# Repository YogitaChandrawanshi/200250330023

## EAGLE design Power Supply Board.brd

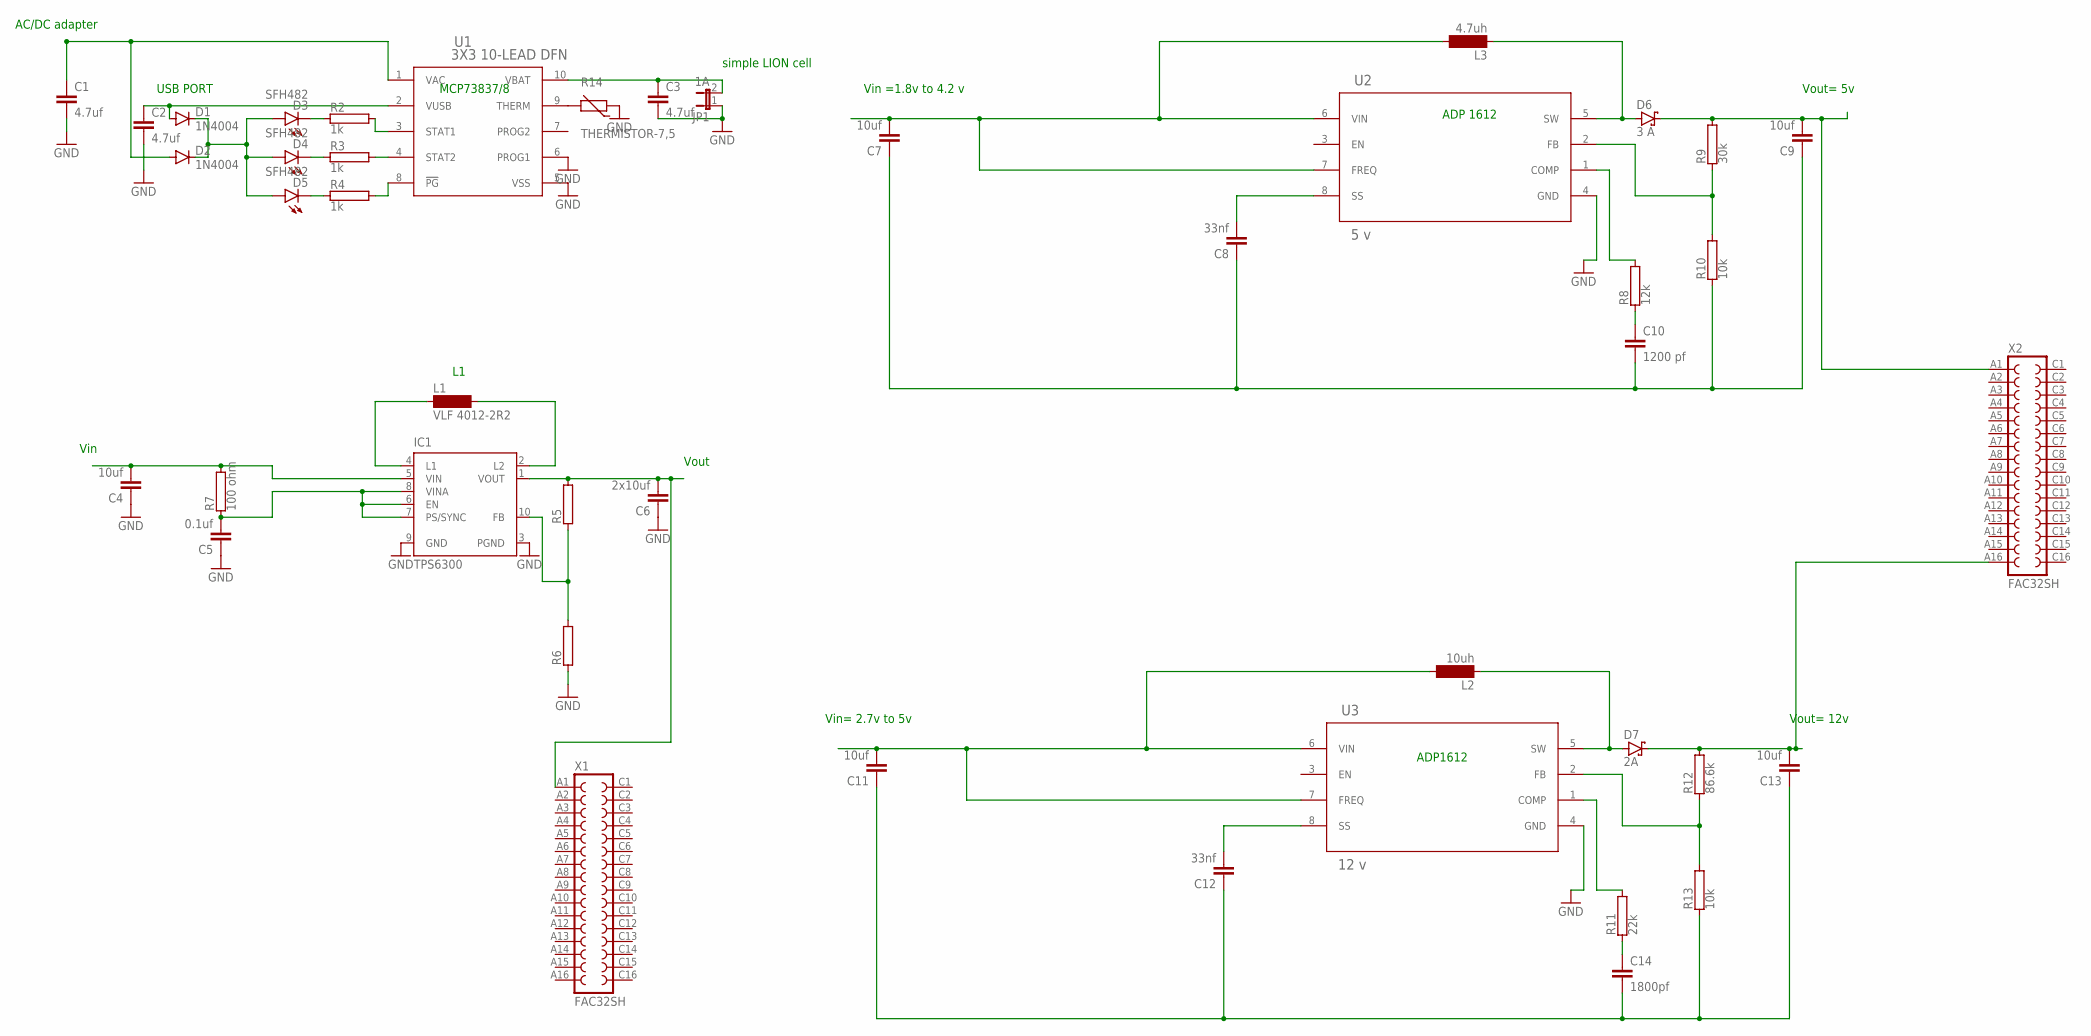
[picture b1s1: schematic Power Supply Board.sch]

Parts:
C1, C2, C3: 4.7uf; C2.5-3
C4, C7, C9, C11, C13: 10uf; C2.5-3
C5: 0.1uf; C2.5-3
C6: 2x10uf; C2.5-3
C8, C12: 33nf; C2.5-3
C10: 1200 pf; C2.5-3
C14: 1800pf; C2.5-3
D1, D2: 1N4004; DO41-10
D3, D4, D5: SFH482
D6: 3 A; C4111-15
D7: 2A; C4111-15
IC1: TPS6300; DRC-S-PVSON-N10
JP1: 1A; JP1
L1: VLF 4012-2R2; MS85
L2: 10uh; MS42
L3: 4.7uh; MS42
R2, R3, R4: 1k; AC01
R5, R6: RAC01; AC01
R7: 100 ohm; AC01
R8: 12k; AC01
R9: 30k; AC01
R10, R13: 10k; AC01
R11: 22k; AC01
R12: 86.6k; AC01
R14: THERMISTOR-7,5; R-7,5
U1: 3X3 10-LEAD DFN; MSOP10_MC_MCH
U2: 5 v; RM_8_ADI
U3: 12 v; RM_8_ADI
X1, X2: FAC32SH

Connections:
GND: C1.2, C2.2, C3.2, C4.1, C5.1, C6.1, IC1.3 (PGND), IC1.9 (GND), JP1.1, R6.1, R14.1, U1.5 (VSS), U1.6 (PROG1), U2.4 (GND), U3.4 (GND)
unnamed: R14.2, U1.9 (THERM)
unnamed: C1.1, D2.A, U1.1 (VAC)
unnamed: C2.1, D1.A, U1.2 (VUSB)
unnamed: D1.C, D2.C, D3.A, D4.A, D5.A
unnamed: C5.2, IC1.6 (EN), IC1.7 (PS/SYNC), IC1.8 (VINA), R7.1
unnamed: D3.K (C), R2.1
unnamed: D4.K (C), R3.1
unnamed: D5.K (C), R4.1
unnamed: R2.2, U1.3 (STAT1)
unnamed: R3.2, U1.4 (STAT2)
unnamed: R4.2, U1.8 (!PG)
unnamed: C3.1, JP1.2, U1.10 (VBAT)
unnamed: C4.2, IC1.5 (VIN), R7.2
unnamed: IC1.4 (L1), L1.1
unnamed: IC1.2 (L2), L1.2
unnamed: C6.2, IC1.1 (VOUT), R5.2, X1.A1
unnamed: IC1.10 (FB), R5.1, R6.2
unnamed: C7.2, L3.2, U2.6 (VIN), U2.7 (FREQ)
unnamed: D6.A, L3.1, U2.5 (SW)
unnamed: C9.2, D6.C, R9.2, X2.A1
unnamed: R9.1, R10.2, U2.2 (FB)
unnamed: R8.2, U2.1 (COMP)
unnamed: C8.2, U2.8 (SS)
unnamed: C7.1, C8.1, C9.1, C10.2, R10.1
unnamed: C10.1, R8.1
unnamed: C11.2, L2.2, U3.6 (VIN), U3.7 (FREQ)
unnamed: D7.A, L2.1, U3.5 (SW)
unnamed: C13.2, D7.C, R12.2, X2.A16
unnamed: R12.1, R13.2, U3.2 (FB)
unnamed: R11.2, U3.1 (COMP)
unnamed: C12.2, U3.8 (SS)
unnamed: C11.1, C12.1, C13.1, C14.2, R13.1
unnamed: C14.1, R11.1

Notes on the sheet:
AC/DC adapter
USB PORT
simple LION cell
MCP73837/8
Vin
Vout
Vin =1.8v to 4.2 v
Vout= 5v
Vin= 2.7v to 5v
Vout= 12v
ADP 1612
ADP1612

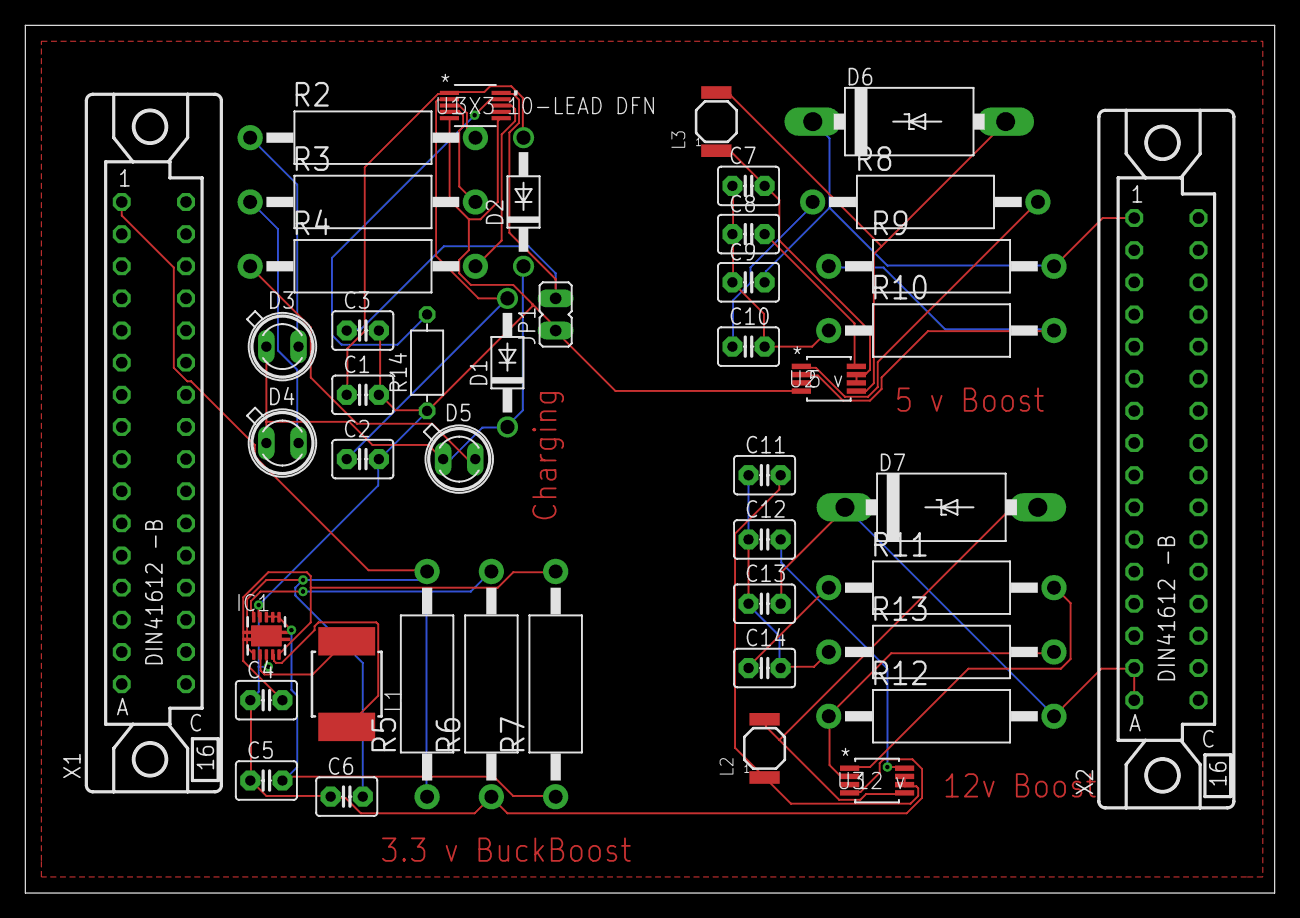
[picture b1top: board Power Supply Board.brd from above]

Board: 2 copper layers, 98.7 x 68.6 mm, 44 parts (0 on the bottom side), 34 nets.
